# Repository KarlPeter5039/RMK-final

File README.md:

# RMK-final
Final iteration of the Reconfigurable Mechanical Keyboard including firmware and PCB files

Developed at Lehigh University for ECE 258 by Sumin Lim '23 and Karl Peter '23

# Abstract
This project aims to explore new and innovative approaches to keyboard design, with a focus on improving user experience by integrating a modular configuration that can be flexible with user needs. The report begins by introducing our initial design, functionality, and how it improves. Communication between modules is made possible by I2C via TRRS jacks. The report then discusses the development process of this project. This includes hardware and software specifications, ethical aspects, altercations that were made, and discussion of the final design. The last section of this report explores future work or adjustments that could be made to further enhance this project. Overall, this project report demonstrates the value of innovative approaches to keyboard design and highlights the potential for future developments in this field.

# Introduction
Anyone can go out and buy a keyboard, but most are fixed designs/sizes and lack functions that are desirable to those who need them. With a modular configuration, a reconfigurable keyboard is all-in-one and can scale up or down, depending on the task, at any time. This is achieved through a magnetic connection with detachable data pins between modules. The final project will include the following modules: left hand master, right hand, number row, function row, analog knob input cluster, slide potentiometer cluster, arrow key cluster with OLED display, and the number pad.

While there have been many designs for modular keyboards, nothing out there really comes close to the practicality of our design. It will be different from generic commercial designs by adding additional peripherals including rotary encoders for analog input, a fully modular set up, and dedicated keyboard portions that can be connected and disconnected at any time. 

# Technical Specifications
## Hardware Specifications:
- Elite-C Microcontrollers - ATmega32U4-based processor at 16MHz with 32KB of flash storage, 26 GPIO pins, and tactile reset button
- Diodes - To prevent back-currents in the keyboard matrix
- TRRS jacks - For I2C connection of modules carrying 4 wires
- Pull-up resistors - 4.7k ohm connected from VCC to SDA and SCL for I2C
- 128X32 OLED screen - Display for words per minute count and bongo cat
- Switches - Digital Cherry MX-based Switches
- Slide Potentiometer - Analog slide input for relative positioning input
- Rotary Encoders - Analog rotating potentiometer inputs for absolute positioning input
- Keyboard plate - 3D printed to mechanically support switches
- PCBs - Designed in KiCAD and ordered from JLCPCB

## Firmware Specifications:
The firmware for a keyboard consists of four primary files: 
- keymap.c: Defines the key mapping of the keyboard
- config.h: Defines the low-level configuration for the keyboard
- rules.mk: Defines the parameters of the ATMega32u4 controller 
- info.json: Defines the physical keyboard layout visually in JavaScript

QMK Firmware was used to configure the keymap, matrix with corresponding rows and columns, and assign keycodes for each of the switches on the keyboard. These files were then flashed to the microcontroller's memory.

### Required software
- QMK MSYS to compile the .c, .h, .mk. and .json files into a single hex file
- QMK Toolbox to flash the compiled hex file to the microcontroller over USB (lots of good tutorials on this)

On the Arduino Pro Micro/Elite-C, I2C is supported through pins PD1, PD0, GND, and VCC (additional pull-up resistors were required). This connection can be achieved through two 4-pin TRRS jacks with a 3.5mm cable. Most of I2C communication lies in the keyboard firmware in the keymap file (.c), config header file (.h), and the rules file (.mk). The left hand module can function on its own, but without it, the rest of the modules would fail to operate.

# Future Work
We chose to take a simplified approach to our original project plan due to potential hardware address limitations in QMK for 8 modules. We concluded that it would be better to have a couple working modules as opposed to 8 non-working ones. For our final keyboard, we cut the modules to just a left and right half but still included an OLED screen, digital switches, slide potentiometer, and rotary encoders. For future works, this keyboard can potentially expand to our initial goal of the 8 modules specified.

Additionally, to manufacture this keyboard on a larger scale, we have the following design altercations in mind: Breaking away from the Breakout Board, ISP (In-System Programming), Independent Molex/USB/Aviator connection, and LED indicators for boot status/flashing.

### Breaking away from the Breakout Board: 
It is far easier and cheaper to mass produce the PCB without the Arduino/Elite-C breakout boards that house the ATMega32U4 microprocessor. SMD components would be used with an on-board clock at 16MHz, capacitors for phase inversion, and bypass capacitors between Vcc and GND to reduce switching noise.

### ISP (In-System Programming): 
This allows quick flashing of the device with firmware without a direct USB connection. This is ideal in a factory environment where it’s impractical to plug each freshly soldered PCB with a USB connection. Instead, a 6 pin ISP connection will be mounted on the board for device access.
Independent Molex/USB/Aviator connection: This is required when eliminating the breakout board. D+ and D- data connections will be soldered to the connectors to further streamline production and reduce costs at a larger scale.

### LED indicators for boot status/flashing: 
A two LED setup will be used for when the keyboard’s memory is being wiped and when the keyboard is successfully and continuously connected with no errors. This will add two additional resistors for each LED.

# Building your own RMK

## Bill of Materials (BOM)
| Component Name          | Quantity |
|     :----------:        |  :----:  |
| Elite-C Microcontrollers| 2x       |
| 1N4148 Diodes           | 63x      |
| TRRS PJ-320A jacks      | 2x       |
| 4.7k resistors          | 2x       |
| 128x32 OLED screen      | 1x       | 
| 10k Slide Potentiometer | 1x       |
| EC11 Rotary Encoders    | 3x       |
| Mechanical Switches     | 63x      |
| Left Keyboard Plate     | 1x       |
| Right Keyboard Plate    | 1x       |
| Keyboard PCB            | 1x       |

To order and build your own RMK, you'll have to source the above components on your own. Good keyboard part vendors include [Keebio](https://keeb.io/), [Aliexpress](https://www.aliexpress.com/), [DigiKey](https://www.digikey.com/), [Little Keyboards](https://www.littlekeyboards.com/), [Custom KBD](https://customkbd.com/), and [Amazon](https://www.amazon.com/ref=nav_logo).
Here, you can obtain most common items such as diodes, microcontrollers, TRRS jacks, and more.

For the PCB, download the PCB gerber and drill files from the repository and upload them to [JLCPCB](https://jlcpcb.com/) and order the 2-layer PCB (minimum order quantity should be around ~5 PCBs. Keyboard plates can be designed by hand or 3D printed if you're fancy.

To build the keyboard: a good approach is to first flash the microcontrollers with firmware to test their functionality and return them if they do not work. After that, solder components while periodically testing the board for functionality (shorting key pins with diodes, turning the rotary encoders, sliding the analog slider, etc.). Hopefully, after some sweat and hopefully no tears, you'll have your own working RMK! Firmware can additionally be customized to your liking by editting the various provided files and compiling them using QMK MSYS + flashing with QMK Toolbox. 

Customization includes 
- Custom keymaps
- Custom rotary encoder functions
- Custom OLED image/animation/information display
- Special macro keys
- Additional layers
- Mapping of analog slider
- Endless possibilities (possibly)

# Acknowledgements
Thank you to Professor Khazaei, Professor Cutitaru, Professor Norian, Ted Bowen, Xiyuan, and Kelly Zona for their help, feedback, and guidance for this project throughout the course of the year.

This is a completed project with no intentions to add or revise. If you have any questions or comments, you can reach me at karlpeteryu@gmail.com

# References
“Designing F13 WKL Tkl Keyboard in Fusion 360”, Zlane - YouTube.com
https://www.youtube.com/watch?v=pvVdCHGJLY4

“A modern handwiring guide - stronger, cleaner, easier”, cribbit - geekhack.com
https://geekhack.org/index.php?topic=87689.0

“Building a Split Keyboard part 2”, Mark Story - mark-story.com
https://mark-story.com/posts/view/building-a-split-keyboard-part-2

“Rotary Encoder + Button Keyboard Output (Arduino Pro Micro)”, dkgrieshammer - Github
https://gist.github.com/dkgrieshammer/66cce6ec92a6427c16804df84c22cc83

“Adding SSD1306 OLED display to your build”, u/ishtob - Reddit
https://www.reddit.com/r/olkb/comments/5zy7og/adding_ssd1306_oled_display_to_your_build/

“Pheromone Keyboard”, luantty2 - Github
https://github.com/luantty2/pheromone_keyboard

“I2C Wiring for Splits”, u/VexillaVexme - Reddit
https://www.reddit.com/r/ErgoMechKeyboards/comments/k4x0a7/i2c_wiring_for_splits/

“A Complete Guide to Building a Hand-Wired Keyboard”, Ben Chapman - crackedthecode.com
https://www.crackedthecode.co/a-complete-guide-to-building-a-hand-wired-keyboard/#hardware-needed

“QMK Feature Options”, QMK group - docs.qmk.fm
https://docs.qmk.fm/#/config_options?id=feature-options

“Lily58 project”, F_YUUCHI - Ortholinear column-staggeredの分割キーボード
https://kata0510.github.io/Lily58-Document/

“Litl keyboard”, mohoyt - Github
https://github.com/mohoyt/litl

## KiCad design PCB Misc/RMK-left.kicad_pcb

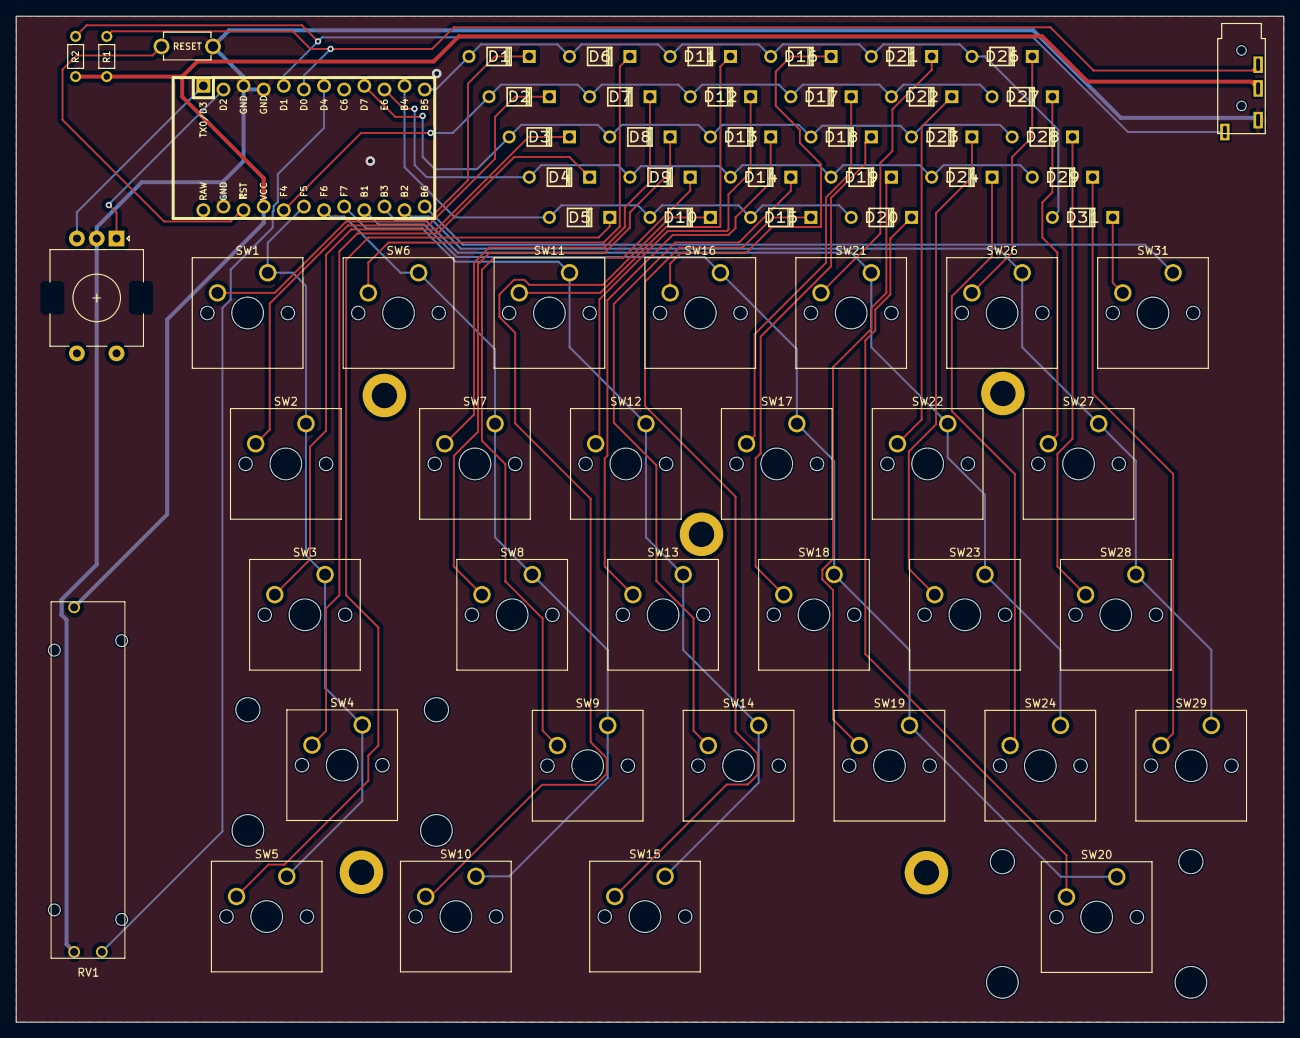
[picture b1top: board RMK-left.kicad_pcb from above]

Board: 2 copper layers, 160.0 x 127.0 mm, 65 parts (1 on the bottom side), 49 nets.

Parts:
D1, D2, D3, D4, D5, D6, D7, D8, D9, D10, D11, D12, D13, D14, D15, D16, D17, D18, D19, D20, D21, D22, D23, D24, D26, D27, D28, D29, D31: D_Small; Diode
R1, R2: 4.7k; RESISTOR
ROT1: RotaryEncoder; RotaryEncoder_EC11
RV1: R_Potentiometer; potentiometer_slider_45mm
SW1, SW6, SW7, SW8, SW9, SW11, SW12, SW13, SW14, SW16, SW17, SW18, SW19, SW21, SW22, SW23, SW24, SW26, SW27, SW28, SW29, SW31: KEYSW; SW_Cherry_MX_1.00u_PCB
SW2: KEYSW; SW_Cherry_MX_1.50u_PCB
SW3: KEYSW; SW_Cherry_MX_1.75u_PCB
SW4, SW20: KEYSW; SW_Cherry_MX_2.25u_PCB
SW5, SW10, SW15: KEYSW; SW_Cherry_MX_1.25u_PCB
SW_A1: SW_PUSH; TACT_SWITCH_TVBP06
U1: ProMicro; ArduinoProMicro-ZigZag
U2: 4PIN; TRRS

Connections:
GND: ROT1.C, RV1.1, SW_A1.2, U1.3 (GND), U1.4 (GND), U1.23 (GND), U2.1 (SLEEVE)
unnamed: D1.2 (A), SW1.2
unnamed: D2.2 (A), SW2.2
unnamed: D3.2 (A), SW3.2
unnamed: D4.2 (A), SW4.2
unnamed: D5.2 (A), SW5.2
unnamed: D6.2 (A), SW6.2
unnamed: D7.2 (A), SW7.2
unnamed: D8.2 (A), SW8.2
unnamed: D9.2 (A), SW9.2
unnamed: D10.2 (A), SW10.2
unnamed: D11.2 (A), SW11.2
unnamed: D12.2 (A), SW12.2
unnamed: D13.2 (A), SW13.2
unnamed: D14.2 (A), SW14.2
unnamed: D15.2 (A), SW15.2
unnamed: D16.2 (A), SW16.2
unnamed: D17.2 (A), SW17.2
unnamed: D18.2 (A), SW18.2
unnamed: D19.2 (A), SW19.2
unnamed: D20.2 (A), SW20.2
unnamed: D21.2 (A), SW21.2
unnamed: D22.2 (A), SW22.2
unnamed: D23.2 (A), SW23.2
unnamed: D24.2 (A), SW24.2
unnamed: D26.2 (A), SW26.2
unnamed: D27.2 (A), SW27.2
unnamed: D28.2 (A), SW28.2
unnamed: D29.2 (A), SW29.2
unnamed: D31.2 (A), SW31.2
SCL: R1.2, U1.6 (3/PD0), U2.3 (RING1)
SDA: R2.2, U1.5 (2/PD1), U2.4 (RING2)
VCC: R1.1, R2.1, RV1.3, U1.21 (VCC), U2.2 (TIP)
col1: SW1.1, SW2.1, SW3.1, SW4.1, SW5.1, U1.19 (A2/PF5)
col2: SW6.1, SW7.1, SW8.1, SW9.1, SW10.1, U1.18 (A1/PF6)
col3: SW11.1, SW12.1, SW13.1, SW14.1, SW15.1, U1.17 (A0/PF7)
col4: SW16.1, SW17.1, SW18.1, SW19.1, SW20.1, U1.16 (15/PB1)
col5: SW21.1, SW22.1, SW23.1, SW24.1, U1.15 (14/PB3)
col6: SW26.1, SW27.1, SW28.1, SW29.1, U1.14 (16/PB2)
col7: SW31.1, U1.13 (10/PB6)
encA: ROT1.B, U1.1 (TX0/PD3)
encB: ROT1.A, U1.2 (RX1/PD2)
reset: SW_A1.1, U1.22 (RST)
rowA: D2.1 (K), D7.1 (K), D12.1 (K), D17.1 (K), D22.1 (K), D27.1 (K), U1.20 (A3/PF4)
rowB: D3.1 (K), D8.1 (K), D13.1 (K), D18.1 (K), D23.1 (K), D28.1 (K), U1.9 (6/PD7)
rowC: D4.1 (K), D9.1 (K), D14.1 (K), D19.1 (K), D24.1 (K), D29.1 (K), U1.10 (7/PE6)
rowD: D5.1 (K), D10.1 (K), D15.1 (K), D20.1 (K), U1.11 (8/PB4)
rowE: D1.1 (K), D6.1 (K), D11.1 (K), D16.1 (K), D21.1 (K), D26.1 (K), D31.1 (K), U1.12 (9/PB5)
slidePot: RV1.2, U1.7 (4/PD4)

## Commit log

2023-09-10 RMK Final Project
    Includes RMK firmware to be complied with QMK MSYS, all PCB files including gerbers and drill files, and partial lowprofile keyboard CHOC switch files
2023-09-15 added bill of materials
2023-09-20 added detail for fabrication and required parts/software
